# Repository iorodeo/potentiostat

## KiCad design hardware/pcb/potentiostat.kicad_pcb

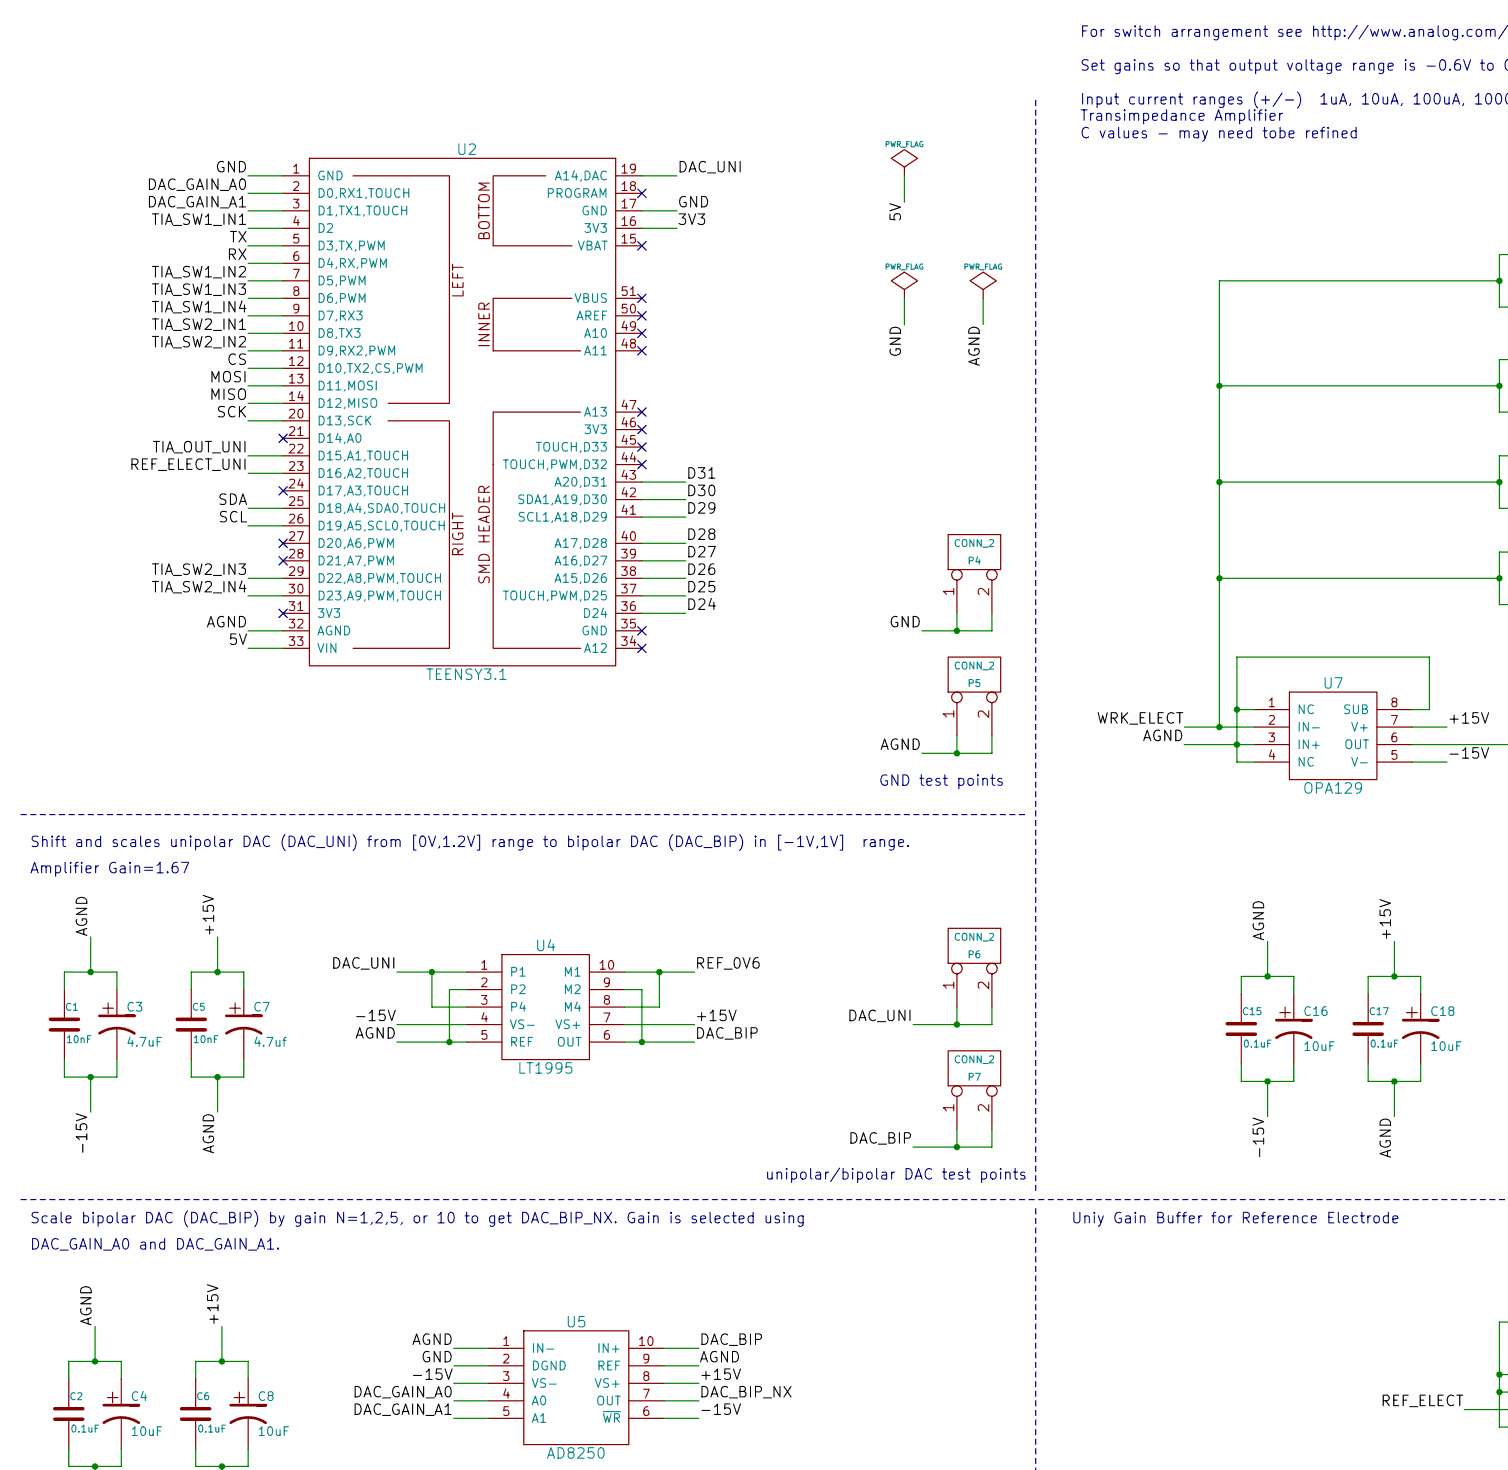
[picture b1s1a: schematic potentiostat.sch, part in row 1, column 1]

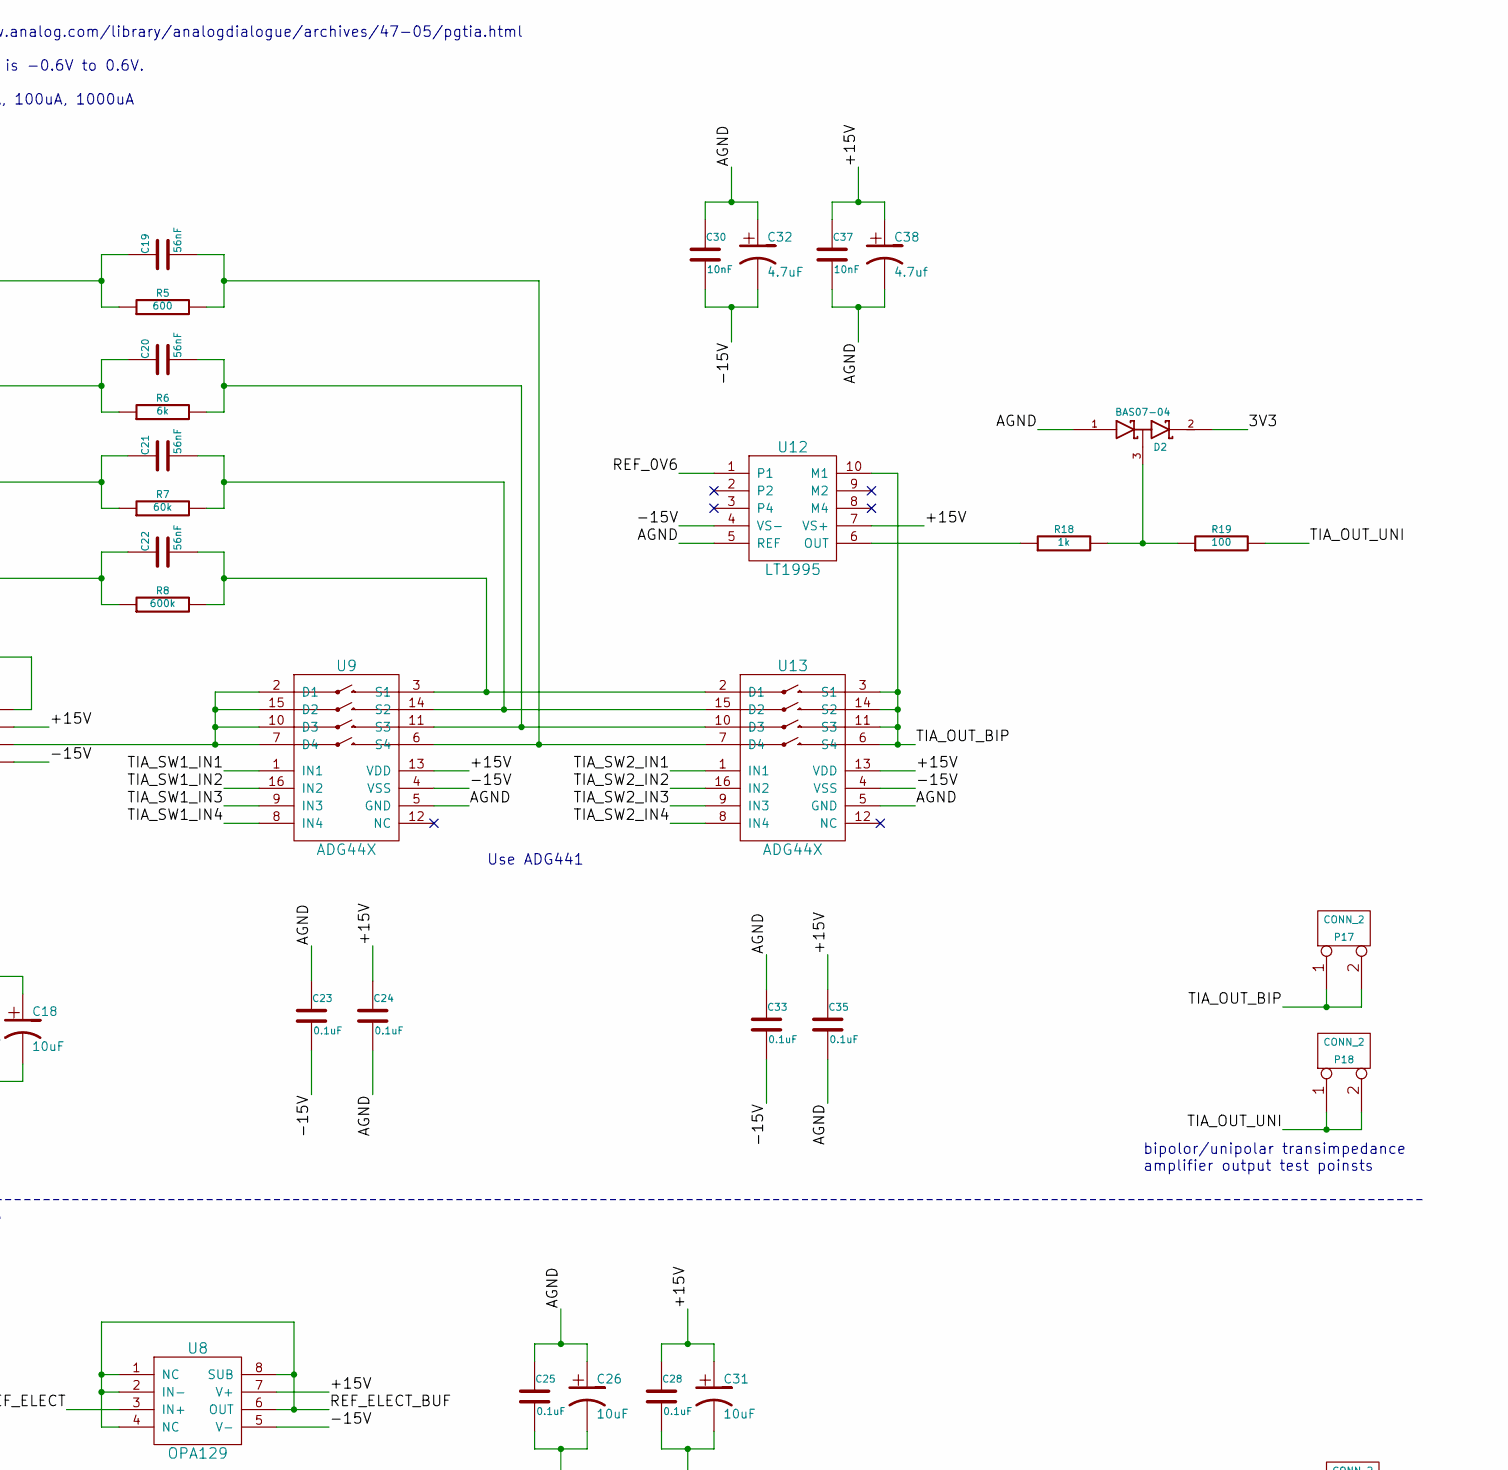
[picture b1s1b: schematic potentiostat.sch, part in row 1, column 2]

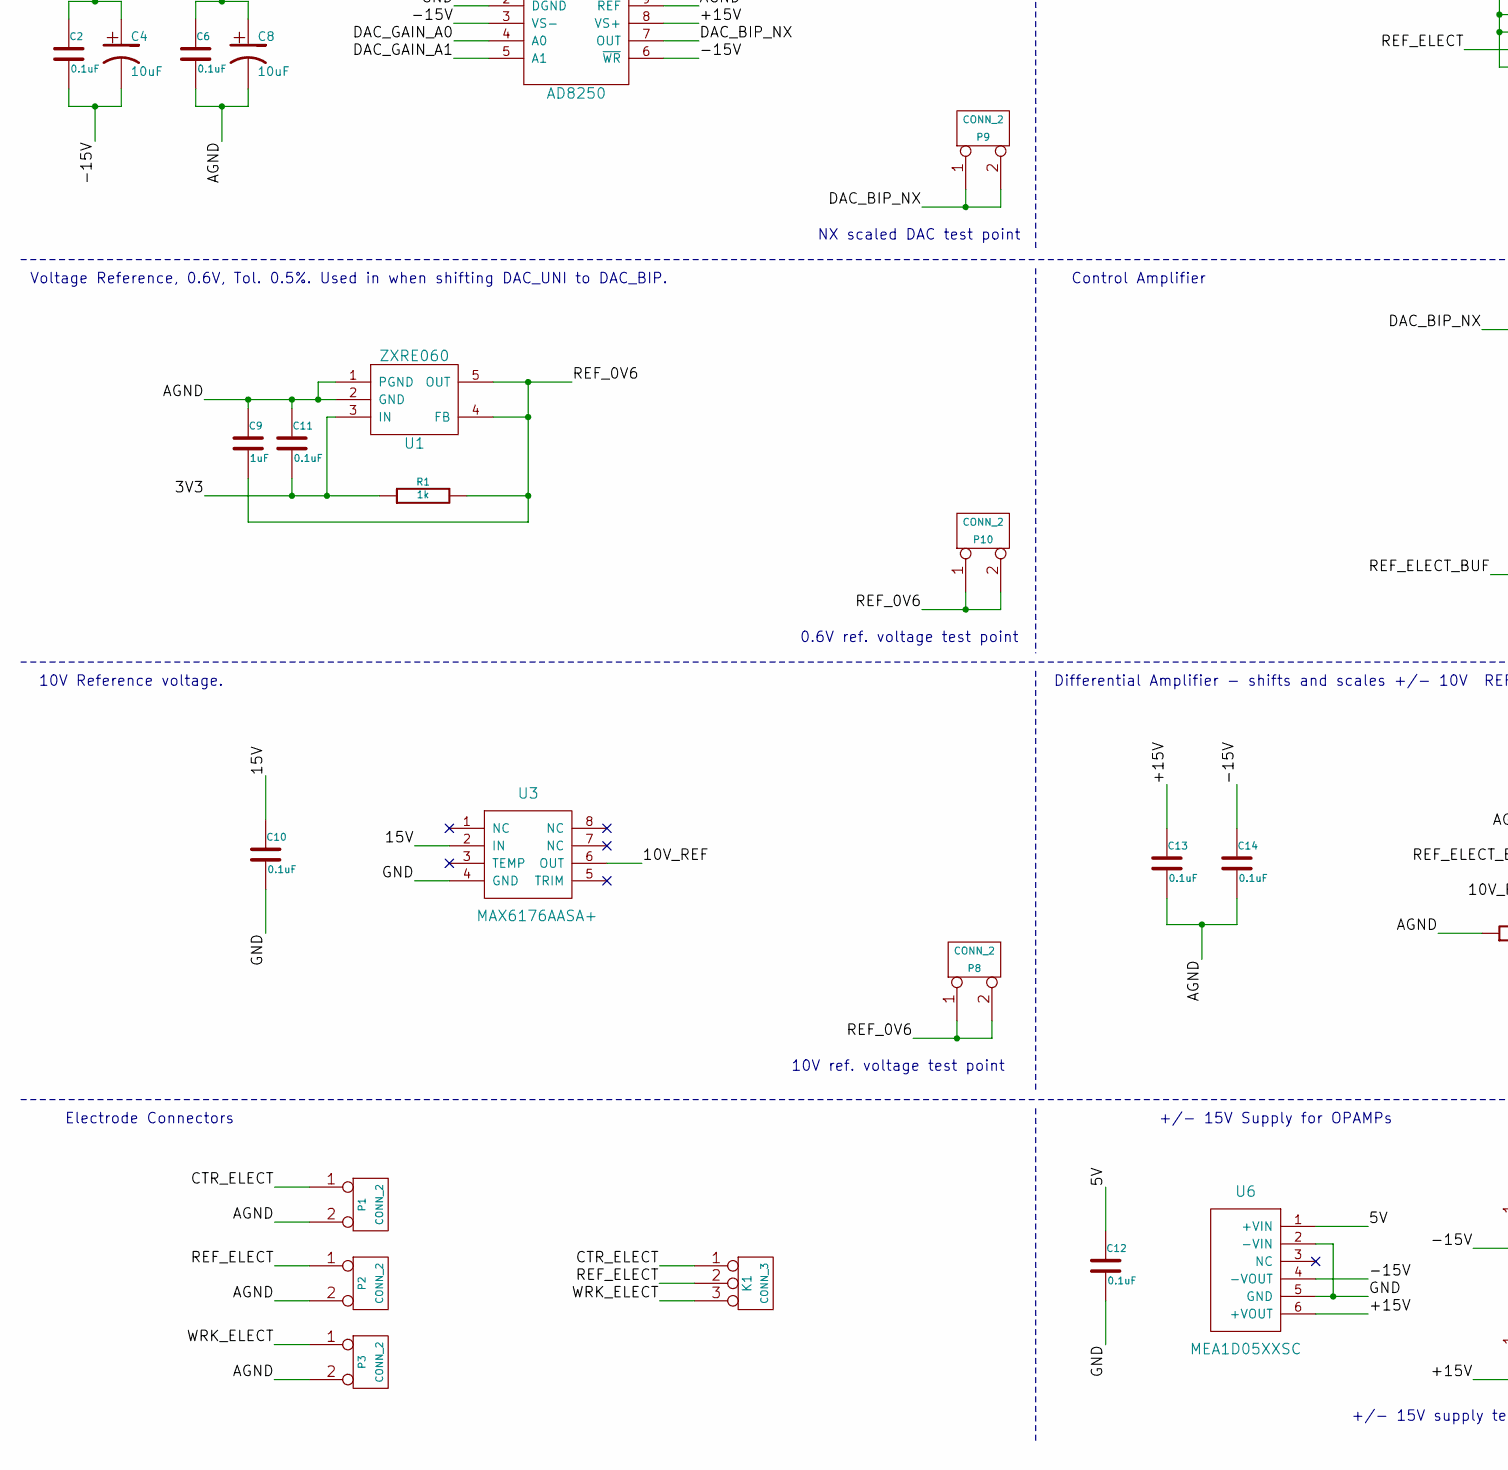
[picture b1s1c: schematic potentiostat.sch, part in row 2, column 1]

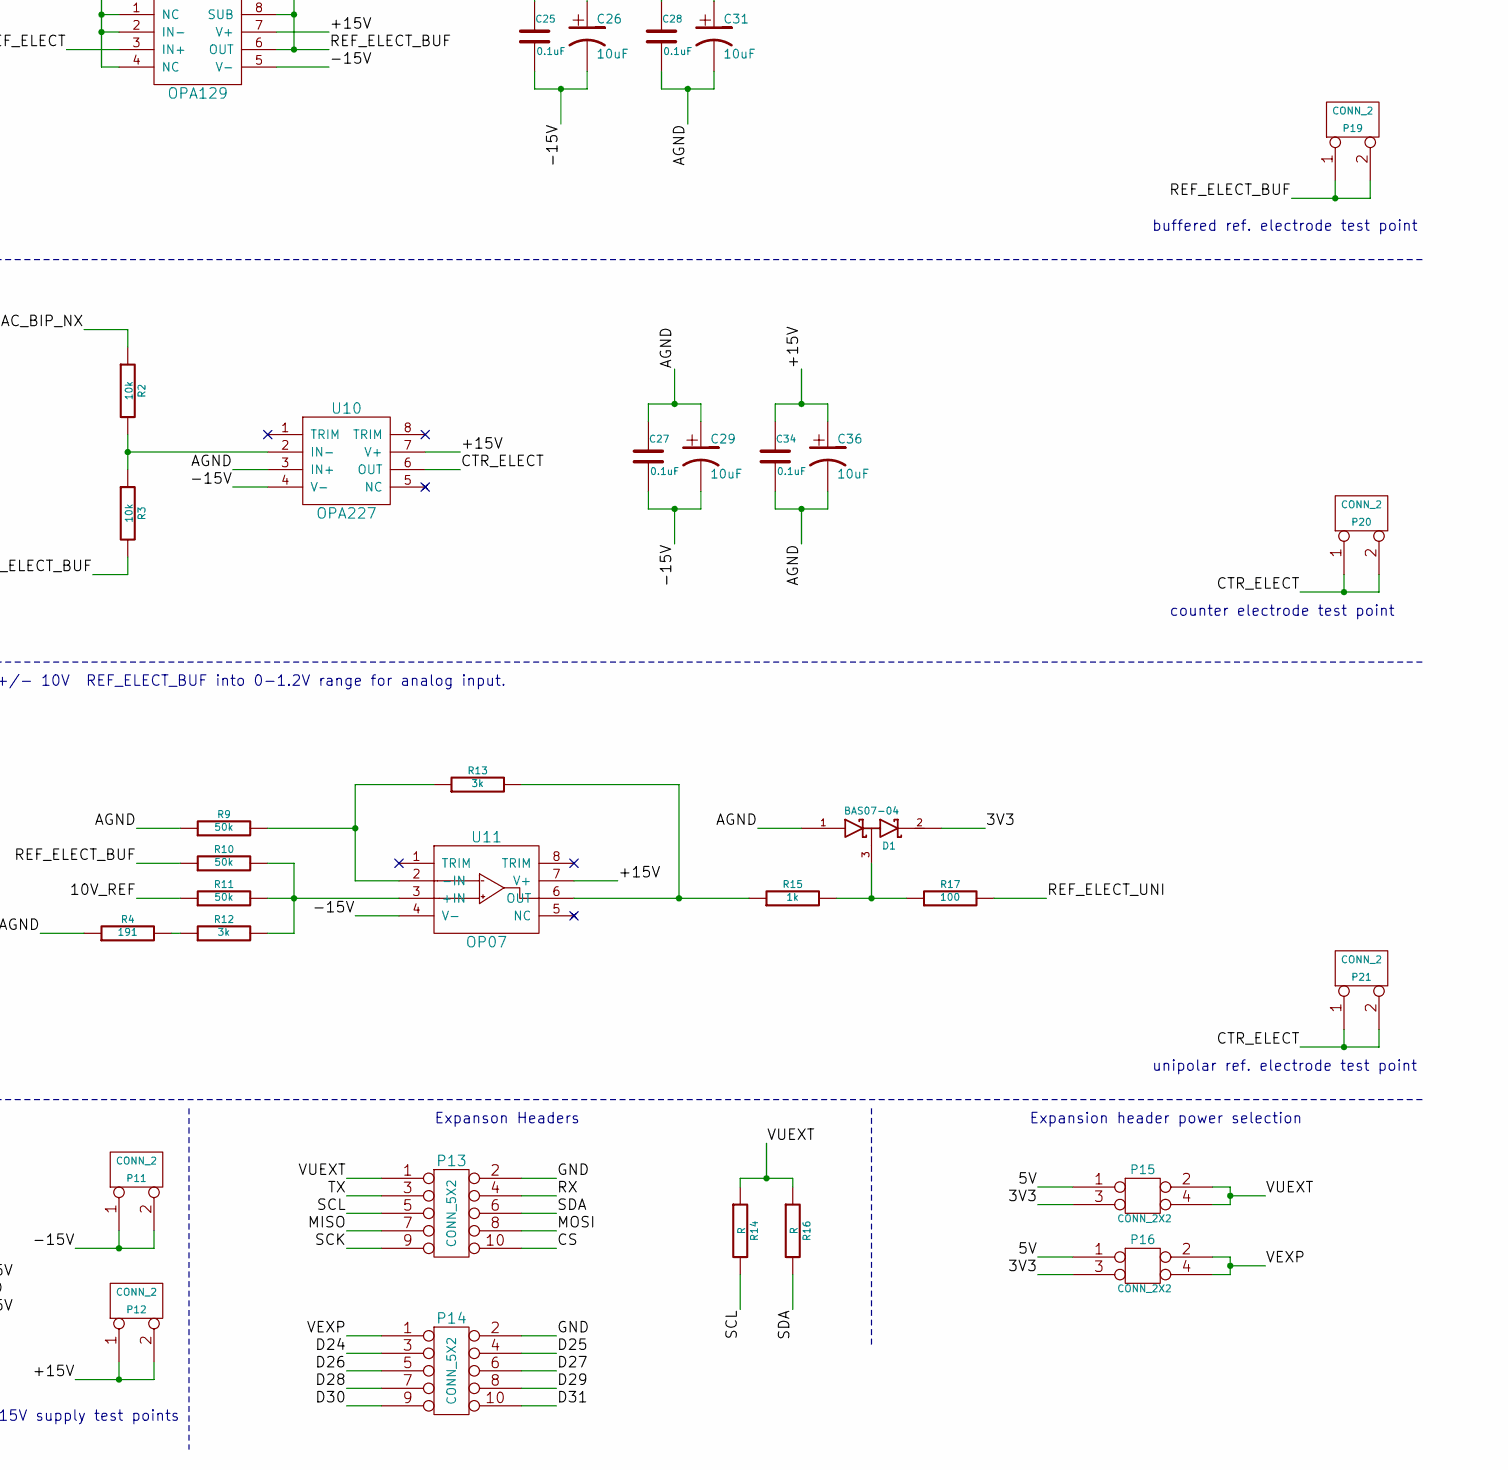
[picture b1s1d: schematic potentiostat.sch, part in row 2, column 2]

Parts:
C1, C5, C30, C37: 10nF
C2, C6, C10, C11, C12, C13, C14, C15, C17, C23, C24, C25, C27, C28, C33, C34, C35: 0.1uF
C3, C32: 4.7uF
C4, C8, C16, C18, C26, C29, C31, C36: 10uF
C7, C38: 4.7uf
C9: 1uF
C19, C20, C21, C22: 56nF
D1, D2: BAS07-04
K1: CONN_3
P1, P2, P3, P4, P5, P6, P7, P8, P9, P10, P11, P12, P17, P18, P19, P20, P21: CONN_2
P13, P14: CONN_5X2
P15, P16: CONN_2X2
R1, R15, R18: 1k
R2, R3: 10k
R4: 191
R5: 600
R6: 6k
R7: 60k
R8: 600k
R9, R10, R11: 50k
R12, R13: 3k
R14, R16: R
R17, R19: 100
U1: ZXRE060
U2: TEENSY3.1
U3: MAX6176AASA+
U4, U12: LT1995
U5: AD8250
U6: MEA1D05XXSC
U7, U8: OPA129
U9, U13: ADG44X
U10: OPA227
U11: OP07

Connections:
/3V3: C11.2, D1.2 (cathode), D2.2 (cathode), P15.3, P16.3, R1.1, U1.3 (IN), U2.16 (3V3)
/5V: C12.1, P15.1, P16.1, U2.33 (VIN), U6.1 (+VIN)
/15V: C10.1, U3.2 (IN)
/+15V: C5.1, C6.1, C7.1, C8.1, C13.1, C17.1, C18.1, C24.1, C28.1, C31.1, C34.1, C35.1, C36.1, C37.1, C38.1, P12.1, P12.2 (PM), U4.7 (VS+), U5.8 (VS+), U6.6 (+VOUT), U7.7 (V+), U8.7 (V+), U9.13 (VDD), U10.7 (V+), U11.7 (V+), U12.7 (VS+), U13.13 (VDD)
/-15V: C1.2, C2.2, C3.2, C4.2, C14.1, C15.2, C16.2, C23.2, C25.2, C26.2, C27.2, C29.2, C30.2, C32.2, C33.2, P11.1, P11.2 (PM), U4.4 (VS-), U5.3 (VS-), U5.6 (~WR), U6.4 (-VOUT), U7.5 (V-), U8.5 (V-), U9.4 (VSS), U10.4 (V-), U11.4 (V-), U12.4 (VS-), U13.4 (VSS)
/AGND: C1.1, C2.1, C3.1, C4.1, C5.2, C6.2, C7.2, C8.2, C9.1, C11.1, C13.2, C14.2, C15.1, C16.1, C17.2, C18.2, C23.1, C24.2, C25.1, C26.1, C27.1, C28.2, C29.1, C30.1, C31.2, C32.1, C33.1, C34.2, C35.2, C36.2, C37.2, C38.2, D1.1 (Anode), D2.1 (Anode), P1.2 (PM), P2.2 (PM), P3.2 (PM), P5.1, P5.2 (PM), R4.1, R9.1, U1.1 (PGND), U1.2 (GND), U2.32 (AGND), U4.2, U4.5 (REF), U5.1 (IN-), U5.9 (REF), U7.1 (NC), U7.3 (IN+), U7.4 (NC), U7.8 (SUB), U9.5 (GND), U10.3 (IN+), U12.5 (REF), U13.5 (GND)
/CS: P13.10, U2.12 (D10,TX2,CS,PWM)
/D24: P14.3, U2.36 (D24)
/D25: P14.4, U2.37 (TOUCH,PWM,D25)
/D26: P14.5, U2.38 (A15,D26)
/D27: P14.6, U2.39 (A16,D27)
/D28: P14.7, U2.40 (A17,D28)
/D29: P14.8, U2.41 (SCL1,A18,D29)
/D30: P14.9, U2.42 (SDA1,A19,D30)
/D31: P14.10, U2.43 (A20,D31)
/DAC_BIP: P7.1, P7.2 (PM), U4.6 (OUT), U4.9 (M2), U5.10 (IN+)
/DAC_BIP_NX: P9.1, P9.2 (PM), R2.1, U5.7 (OUT)
/DAC_GAIN_A0: U2.2 (D0,RX1,TOUCH), U5.4 (A0)
/DAC_GAIN_A1: U2.3 (D1,TX1,TOUCH), U5.5 (A1)
/DAC_UNI: P6.1, P6.2 (PM), U2.19 (A14,DAC), U4.1, U4.3 (P4)
/GND: C10.2, C12.2, P4.1, P4.2 (PM), P13.2, P14.2, U2.1 (GND), U2.17 (GND), U3.4 (GND), U5.2 (DGND), U6.2 (-VIN), U6.5 (GND)
/MISO: P13.7, U2.14 (D12,MISO)
/MOSI: P13.8, U2.13 (D11,MOSI)
/REF_ELECT: K1.2 (PM), P2.1, U8.3 (IN+)
/REF_ELECT_BUF: P19.1, P19.2 (PM), R3.2, R10.1, U8.1 (NC), U8.2 (IN-), U8.4 (NC), U8.6 (OUT), U8.8 (SUB)
/RX: P13.4, U2.6 (D4,RX,PWM)
/SCK: P13.9, U2.20 (D13,SCK)
/SCL: P13.5, R14.2, U2.26 (D19,A5,SCL0,TOUCH)
/SDA: P13.6, R16.2, U2.25 (D18,A4,SDA0,TOUCH)
/TIA_OUT_BIP: P17.1, P17.2 (PM), U12.10 (M1), U13.3 (S1), U13.6 (S4), U13.11 (S3), U13.14 (S2)
/TIA_OUT_UNI: P18.1, P18.2 (PM), R19.2, U2.22 (D15,A1,TOUCH)
/TIA_SW1_IN1: U2.4 (D2), U9.1 (IN1)
/TIA_SW1_IN2: U2.7 (D5,PWM), U9.16 (IN2)
/TIA_SW1_IN3: U2.8 (D6,PWM), U9.9 (IN3)
/TIA_SW1_IN4: U2.9 (D7,RX3), U9.8 (IN4)
/TIA_SW2_IN1: U2.10 (D8,TX3), U13.1 (IN1)
/TIA_SW2_IN2: U2.11 (D9,RX2,PWM), U13.16 (IN2)
/TIA_SW2_IN3: U2.29 (D22,A8,PWM,TOUCH), U13.9 (IN3)
/TIA_SW2_IN4: U2.30 (D23,A9,PWM,TOUCH), U13.8 (IN4)
/TX: P13.3, U2.5 (D3,TX,PWM)
/VEXP: P14.1, P16.2, P16.4
/VUEXT: P13.1, P15.2, P15.4, R14.1, R16.1
/WRK_ELECT: C19.1, C20.1, C21.1, C22.1, K1.3, P3.1, R5.1, R6.1, R7.1, R8.1, U7.2 (IN-)
unnamed: R18.1, U12.6 (OUT)
unnamed: D2.3 (AK), R18.2, R19.1
unnamed: U7.6 (OUT), U9.2 (D1), U9.7 (D4), U9.10 (D3), U9.15 (D2)
unnamed: R9.2, R13.1, U11.2 (-IN)
unnamed: R4.2, R12.1
unnamed: D1.3 (AK), R15.2, R17.1
unnamed: R13.2, R15.1, U11.6 (OUT)
unnamed: R10.2, R11.2, R12.2, U11.3 (+IN)
unnamed: C19.2, R5.2, U9.6 (S4), U13.7 (D4)
unnamed: C20.2, R6.2, U9.11 (S3), U13.10 (D3)
unnamed: C21.2, R7.2, U9.14 (S2), U13.15 (D2)
unnamed: C22.2, R8.2, U9.3 (S1), U13.2 (D1)
unnamed: R2.2, R3.1, U10.2 (IN-)

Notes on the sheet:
Voltage Reference, 0.6V, Tol. 0.5%. Used in when shifting DAC_UNI to DAC_BIP.
Shift and scales unipolar DAC (DAC_UNI) from [0V,1.2V] range to bipolar DAC (DAC_BIP) in [-1V,1V] range.
Scale bipolar DAC (DAC_BIP) by gain N=1,2,5, or 10 to get DAC_BIP_NX. Gain is selected using
DAC_GAIN_A0 and DAC_GAIN_A1.
Amplifier Gain=1.67
+/- 15V Supply for OPAMPs
Uniy Gain Buffer for Reference Electrode
Control Amplifier
Transimpedance Amplifier
Expanson Headers
Expansion header power selection
Electrode Connectors
For switch arrangement see http://www.analog.com/library/analogdialogue/archives/47-05/pgtia.html Set gains so that output voltage range is -0.6V to 0.6V. Input current ranges (+/-) 1uA, 10uA, 100uA, 1000uA C values - may need tobe refined
GND test points
unipolar/bipolar DAC test points
NX scaled DAC test point
0.6V ref. voltage test point
+/- 15V supply test points
buffered ref. electrode test point
bipolor/unipolar transimpedance amplifier output test poinsts
unipolar ref. electrode test point
10V Reference voltage.
10V ref. voltage test point
Differential Amplifier - shifts and scales +/- 10V REF_ELECT_BUF into 0-1.2V range for analog input.
counter electrode test point
Use ADG441

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
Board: 2 copper layers, 98 parts (0 on the bottom side), 60 nets, no tracks yet.

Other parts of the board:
4-40, 4-40#2, 4-40#3, 4-40#4: VAL**; 4-40

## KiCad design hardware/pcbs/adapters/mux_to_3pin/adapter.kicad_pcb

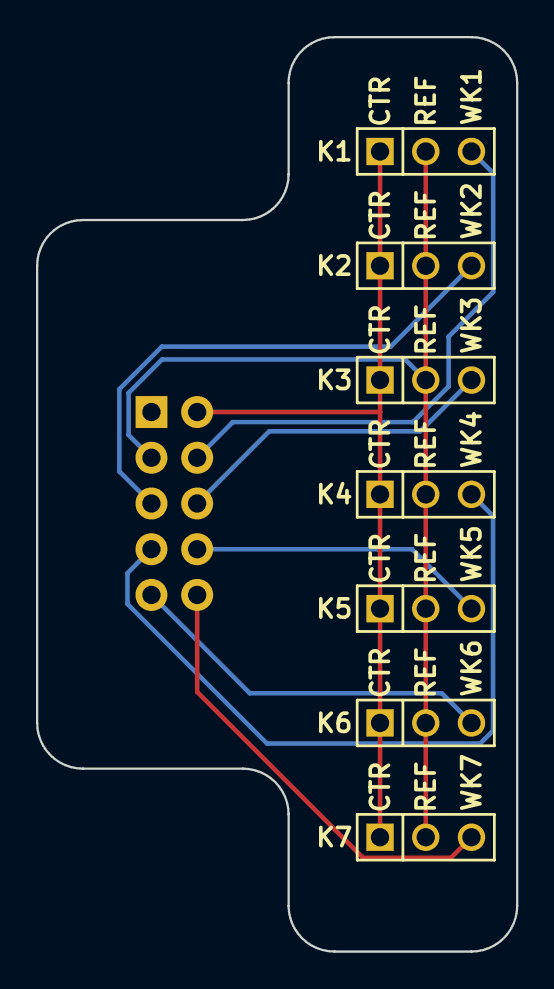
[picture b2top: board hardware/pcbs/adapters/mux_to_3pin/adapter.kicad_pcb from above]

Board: 2 copper layers, 26.7 x 50.8 mm, 8 parts (1 on the bottom side), 9 nets.

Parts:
K1, K2, K3, K4, K5, K6, K7: CONN_3; PIN_ARRAY_3X1
P1: CONN_5X2; 5X2_SHRD_HEADER_FEMALE

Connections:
/CTR_SW: K1.1, K2.1, K3.1, K4.1, K5.1, K6.1, K7.1, P1.2
/REF_SW: K1.2, K2.2, K3.2, K4.2, K5.2, K6.2, K7.2, P1.3
/WRK_1: K1.3, P1.4
/WRK_2: K2.3, P1.5
/WRK_3: K3.3, P1.6
/WRK_4: K4.3, P1.7
/WRK_5: K5.3, P1.8
/WRK_6: K6.3, P1.9
/WRK_7: K7.3, P1.10

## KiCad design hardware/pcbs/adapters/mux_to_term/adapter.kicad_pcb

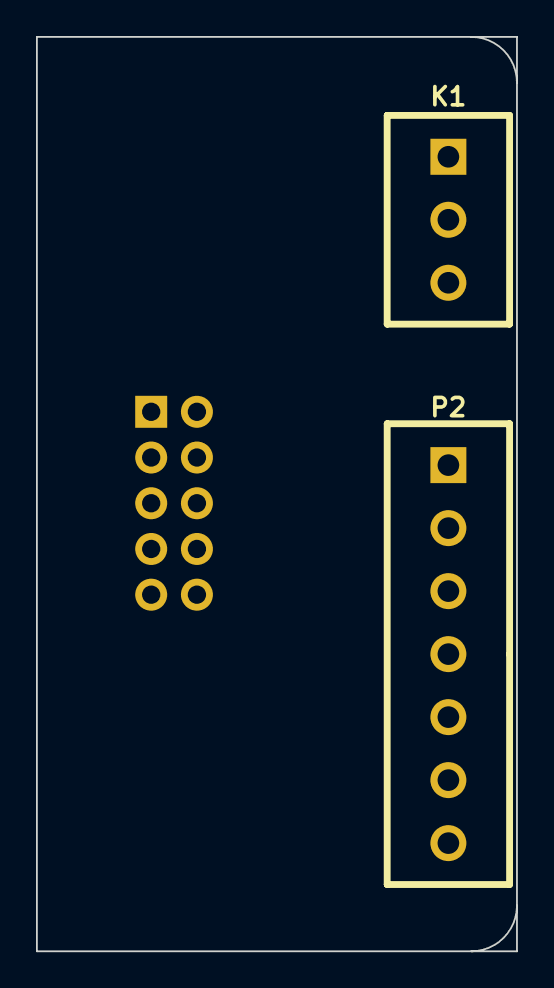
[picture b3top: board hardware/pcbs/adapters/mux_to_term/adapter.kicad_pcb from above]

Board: 2 copper layers, 26.7 x 50.8 mm, 3 parts (1 on the bottom side), 10 nets, no tracks yet.

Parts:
K1: CONN_3; CONNBLOCK3
P1: CONN_5X2; 5X2_SHRD_HEADER_FEMALE
P2: CONN_7; CONNBLOCK7

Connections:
/CTR_SW: K1.2, P1.2
/GND: K1.1, P1.1
/REF_SW: K1.3, P1.3
/WRK_1: P1.4, P2.1
/WRK_2: P1.5, P2.2
/WRK_3: P1.6, P2.3
/WRK_4: P1.7, P2.4
/WRK_5: P1.8, P2.5
/WRK_6: P1.9, P2.6
/WRK_7: P1.10, P2.7

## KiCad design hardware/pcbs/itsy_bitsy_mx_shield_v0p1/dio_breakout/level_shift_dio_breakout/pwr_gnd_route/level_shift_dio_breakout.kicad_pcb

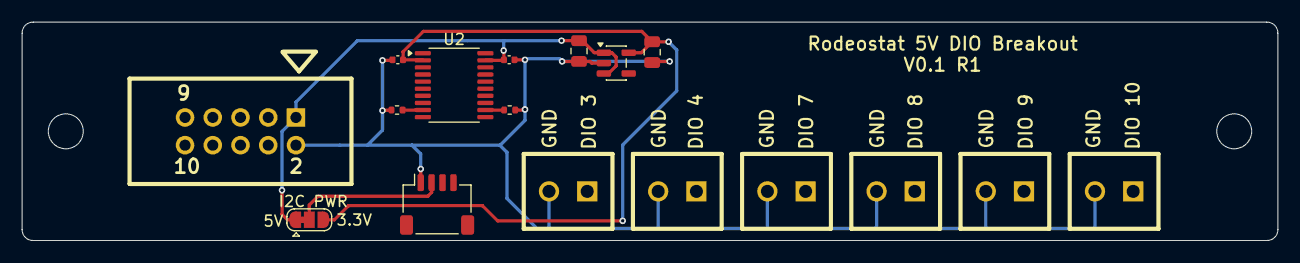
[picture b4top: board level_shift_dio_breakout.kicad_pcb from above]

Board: 2 copper layers, 115.0 x 20.0 mm, 19 parts (0 on the bottom side), 20 nets.

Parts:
C1, C2: 10uF; C_0805_2012Metric
C3, C4: 0.1uF; C_0402_1005Metric
H1, H2: MountingHole; MountingHole_3.2mm_M3
J1: Conn_02x05_Odd_Even; 5X2_SHRD_HEADER
J2: Conn_01x04; JST_SH_SM04B-SRSS-TB_1x04-1MP_P1.00mm_Horizontal
J3, J4, J5, J6, J7, J8: Screw_Terminal_01x02; CONNBLOCK2
JP1: SolderJumper_3_Bridged12; SolderJumper-3_P1.3mm_Bridged12_RoundedPad1.0x1.5mm
R1, R2: 10k; R_0402_1005Metric
U1: AP2112K-3.3; SOT-23-5
U2: TXB0108PW; TSSOP-20_4.4x6.5mm_P0.65mm

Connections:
+3.3V: C2.1, C3.1, JP1.3 (B), U1.5 (VOUT), U2.2 (V_{CCA}), U2.10 (OE)
+5V: C1.1, C4.1, J1.1, JP1.1 (A), U1.1 (VIN), U1.3 (EN), U2.19 (V_{CCB})
/DIO_PIN_3: J1.3, U2.1 (A1)
/DIO_PIN_4: J1.4, U2.3 (A2)
/DIO_PIN_5: J1.5, J2.4
/DIO_PIN_6: J1.6, J2.3
/DIO_PIN_7: J1.7, U2.4 (A3)
/DIO_PIN_8: J1.8, U2.5 (A4)
/DIO_PIN_9: J1.9, U2.6 (A5)
/DIO_PIN_10: J1.10, U2.7 (A6)
/V_I2C: J2.2, JP1.2 (C)
GND: C1.2, C2.2, C3.2, C4.2, J1.2, J2.1, J3.2, J4.2, J5.2, J6.2, J7.2, J8.2, R1.2, R2.2, U1.2 (GND), U2.11 (GND)
unnamed: J3.1, U2.20 (B1)
unnamed: J4.1, U2.18 (B2)
unnamed: J5.1, U2.17 (B3)
unnamed: J6.1, U2.16 (B4)
unnamed: J7.1, U2.15 (B5)
unnamed: J8.1, U2.14 (B6)
unnamed: R1.1, U2.8 (A7), U2.9 (A8)
unnamed: R2.1, U2.12 (B8), U2.13 (B7)

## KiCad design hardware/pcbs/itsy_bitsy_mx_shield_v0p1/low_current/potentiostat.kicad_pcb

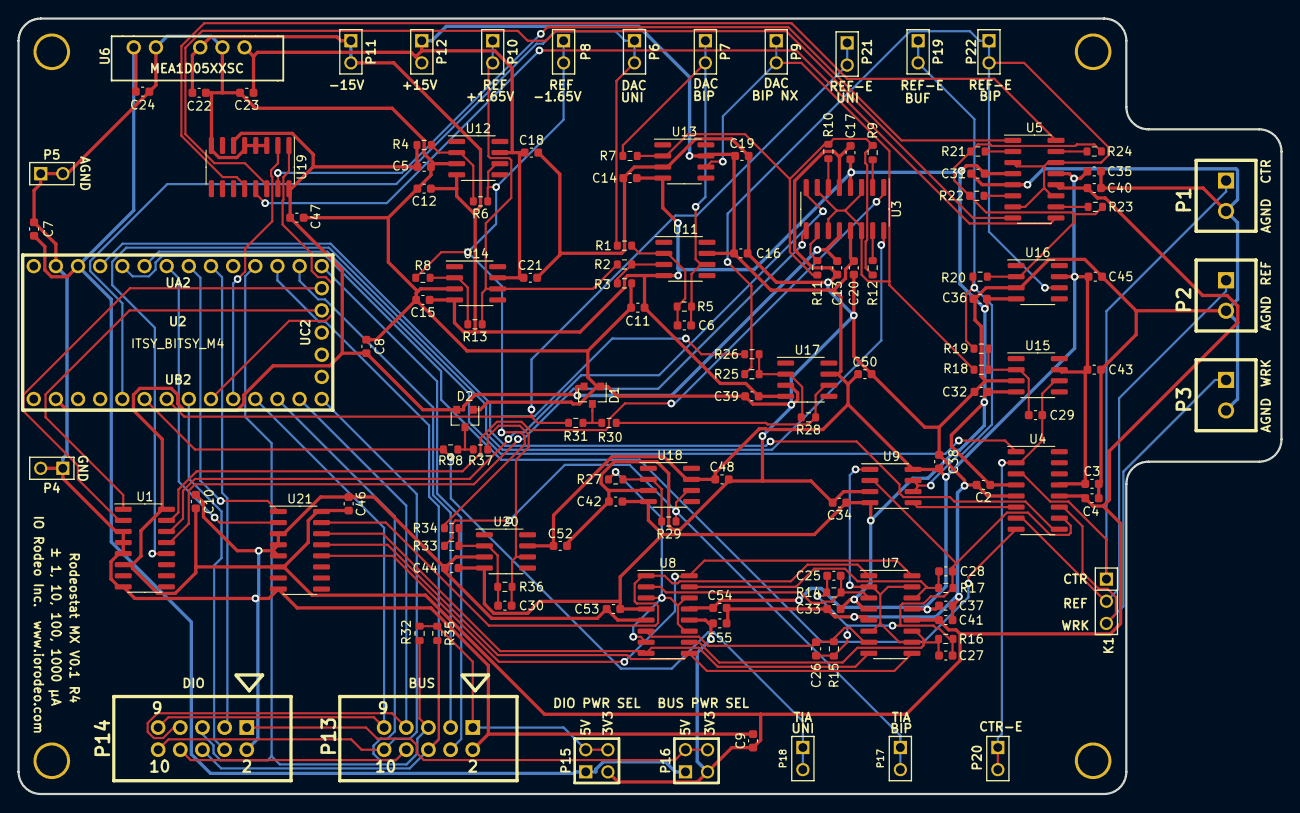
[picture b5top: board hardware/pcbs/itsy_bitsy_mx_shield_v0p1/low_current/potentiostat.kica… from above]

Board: 2 copper layers, 144.8 x 88.9 mm, 142 parts (0 on the bottom side), 82 nets.

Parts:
C2, C3, C4, C10, C11, C12, C13, C14, C15, C16, C17, C18, C19, C20, C21, C24, C31, C32, C33, C34, C35, C36, C37, C38, C39, C40, C41, C42, C43, C44, C45, C46, C47, C48, C50, C52, C53, C54, C55: 0.1uF; C_0603_1608Metric
C5: 4.7uF; C_0603_1608Metric
C6: 3.3nF; C_0603_1608Metric
C7, C8, C9: 2.2uF; C_0603_1608Metric
C22, C23: 1uF; C_0603_1608Metric
C25, C26, C27, C28: 56nF; C_0603_1608Metric
C29: 10nF; C_0603_1608Metric
C30: 12nF; C_0603_1608Metric
D1, D2: BAS07-04; SOT-23
H1, H2, H3, H4: VAL**; 4-40
K1: Conn_01x03; PIN_ARRAY_3X1
P1, P2, P3: Conn_01x02; CONNBLOCK2
P4, P5, P6, P7, P8, P9, P10, P11, P12, P17, P18, P19, P20, P21, P22: Conn_01x02; PIN_ARRAY_2X1
P13, P14: Conn_02x05_Odd_Even; 5X2_SHRD_HEADER
P15, P16: Conn_02x02_Odd_Even; PIN_ARRAY_2X2
R1, R2, R26, R28: 33k; R_0603_1608Metric
R3, R4, R5, R8, R10, R13, R23, R25: 20k; R_0603_1608Metric
R6, R7, R9, R18, R19, R24, R33, R34, R36: 10k; R_0603_1608Metric
R11, R22: 50k; R_0603_1608Metric
R12, R20, R21: 100k; R_0603_1608Metric
R14: 300k; R_0603_1608Metric
R15: 30k; R_0603_1608Metric
R16: 3k; R_0603_1608Metric
R17: 300; R_0603_1608Metric
R27: 2k; R_0603_1608Metric
R29: 11k; R_0603_1608Metric
R30, R37: 1k; R_0603_1608Metric
R31, R38: 100; R_0603_1608Metric
R32, R35: 4.7k; R_0603_1608Metric
U1, U19, U21: 74HC138; SOIC-16_3.9x9.9mm_P1.27mm
U2: ITSY_BITSY_M4
U3, U4, U5, U7, U8: DG411xY; SOIC-16_3.9x9.9mm_P1.27mm
U6: MEA1D05XXSC; MEA1
U9: TL072; SOIC-8_3.9x4.9mm_P1.27mm
U11, U12, U13, U14, U15, U16, U17, U18, U20: OP07; SOIC-8_3.9x4.9mm_P1.27mm
UA2: header_14_pos
UB2: header_14_pos
UC2: header_5_pos

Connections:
/3V3: C4.1, C5.1, C8.1, C9.1, C10.1, C13.1, C40.1, C41.1, C46.1, C47.1, C55.1, D1.2, D2.2, P15.3, P16.3, R4.2, U1.6, U1.16, U2.2, U3.12, U4.12, U5.12, U7.12, U8.12, U19.6, U19.16, U21.6, U21.16
/5V: C7.1, C24.1, P15.1, P16.1, U2.31, U6.1
/+15V: C3.1, C16.1, C18.1, C19.1, C20.1, C21.1, C23.1, C35.1, C37.1, C38.1, C43.1, C45.1, C48.1, C50.1, C52.1, C54.1, P12.1, P12.2, U3.13, U4.13, U5.13, U6.6, U7.13, U8.13, U9.8, U11.7, U12.7, U13.7, U14.7, U15.7, U16.7, U17.7, U18.7, U20.7
/-15V: C2.1, C11.1, C12.1, C14.1, C15.1, C17.1, C22.1, C31.1, C32.1, C33.1, C34.1, C36.1, C39.1, C42.1, C44.1, C53.1, P11.1, P11.2, U3.4, U4.4, U5.4, U6.4, U7.4, U8.4, U9.4, U11.4, U12.4, U13.4, U14.4, U15.4, U16.4, U17.4, U18.4, U20.4
/A3_D17: P14.4, U2.8
/CS: P13.10, P14.10, U2.14
/CTR_ELECT: C29.1, P20.1, P20.2, U4.2, U15.6
/CTR_ELECT_OUT: K1.1, P1.1, U4.3
/D7: P14.3, U2.25
/DAC_BIP: C6.1, P7.1, P7.2, R5.1, R7.2, U11.6
/DAC_BIP_NX: P9.1, P9.2, R18.2, U3.3, U3.7, U3.11, U3.14, U13.6
/DAC_GAIN_A0: U1.1, U2.18
/DAC_GAIN_A1: U1.2, U2.19
/DAC_UNI: P6.1, P6.2, R1.2, U2.5
/GND: C2.2, C3.2, C4.2, C5.2, C7.2, C8.2, C9.2, C10.2, C11.2, C12.2, C13.2, C14.2, C15.2, C16.2, C17.2, C18.2, C19.2, C20.2, C21.2, C22.2, C23.2, C24.2, C31.2, C32.2, C33.2, C34.2, C35.2, C36.2, C37.2, C38.2, C39.2, C40.2, C41.2, C42.2, C43.2, C44.2, C45.2, C46.2, C47.2, C48.2, C50.2, C52.2, C53.2, C54.2, C55.2, D1.1, D2.1, P1.2, P2.2, P3.2, P4.1, P4.2, P5.1, P5.2, P13.2, P14.2, R3.2, U1.3, U1.4, U1.5, U1.8, U2.32, U3.5, U4.5, U5.5, U6.2, U6.5, U7.5, U8.5, U9.3, U12.3, U13.3, U14.3, U15.3, U16.3, U17.3, U18.3, U19.3, U19.4, U19.5, U19.8, U20.3, U21.3, U21.4, U21.5, U21.8
/PICO: P13.8, P14.8, U2.12
/POCI: P13.7, P14.7, U2.13
/REF_1V65: P10.1, P10.2, R2.2, R13.1, U14.6
/REF_ELECT: U4.6, U9.5
/REF_ELECT_BIP: P22.1, P22.2, R25.2, U5.3, U5.7, U5.11, U5.14, U16.6
/REF_ELECT_BUF: P19.1, P19.2, R19.1, R20.2, U9.6, U9.7
/REF_ELECT_OUT: K1.2, P2.1, U4.7
/REF_ELECT_UNI: P21.1, P21.2, R31.1, U2.7
/REF_GAIN_A0: U2.9, U19.1
/REF_GAIN_A1: U2.10, U19.2
/REF_NEG_1V65: P8.1, P8.2, R6.1, R8.2, R26.2, R34.2, U12.6
/RX_D0: P13.4, U2.20
/SCK: P13.9, P14.9, U2.11
/SCL: P13.5, P14.5, R32.2, U2.23
/SDA: P13.6, P14.6, R35.2, U2.22
/SW_CTR_ELECT: U2.28, U4.1
/SW_GAIN_1X: U1.15, U3.1
/SW_GAIN_2X: U1.14, U3.8
/SW_GAIN_5X: U1.13, U3.9
/SW_GAIN_10X: U1.12, U3.16
/SW_GAIN_INV_1X: U5.1, U19.15
/SW_GAIN_INV_2X: U5.8, U19.14
/SW_GAIN_INV_5X: U5.9, U19.13
/SW_GAIN_INV_10X: U5.16, U19.12
/SW_REF_ELECT: U2.29, U4.8
/SW_TIA_GAIN_1: U7.1, U8.1, U21.15
/SW_TIA_GAIN_2: U7.8, U8.8, U21.14
/SW_TIA_GAIN_3: U7.9, U8.9, U21.13
/SW_TIA_GAIN_4: U7.16, U8.16, U21.12
/SW_WRK_ELECT: U2.30, U4.9
/TIA_GAIN_A0: U2.26, U21.1
/TIA_GAIN_A1: U2.27, U21.2
/TIA_OUT_BIP: P17.1, P17.2, R29.1, R33.2, U18.6
/TIA_OUT_UNI: P18.1, P18.2, R38.1, U2.6
/TX_D1: P13.3, U2.21
/VEXP: P14.1, P16.2, P16.4
/VUEXT: P13.1, P15.2, P15.4, R32.1, R35.1
/WRK_ELECT: C25.2, C26.2, C27.2, C28.2, R14.2, R15.2, R16.2, R17.2, U4.10, U9.2
/WRK_ELECT_OUT: K1.3, P3.1, U4.11
unnamed: C6.2, R1.1, R5.2, U11.2
unnamed: C25.1, R14.1, U7.3, U8.2
unnamed: C26.1, R15.1, U7.7, U8.6
unnamed: C27.1, R16.1, U7.11, U8.10
unnamed: C28.1, R17.1, U7.14, U8.15
unnamed: C29.2, R18.1, R19.2, U15.2
unnamed: C30.1, R36.1, R37.2, U20.6
unnamed: C30.2, R33.1, R34.1, R36.2, U20.2
unnamed: D1.3, R30.1, R31.2
unnamed: D2.3, R37.1, R38.2
unnamed: R2.1, R3.1, U11.3
unnamed: R4.1, R6.2, U12.2
unnamed: R9.1, U3.2
unnamed: R10.1, U3.6
unnamed: R7.1, R9.2, R10.2, R11.2, R12.2, U13.2
unnamed: R11.1, U3.10
unnamed: R12.1, U3.15
unnamed: R8.1, R13.2, U14.2
unnamed: R20.1, R21.2, R22.2, R23.2, R24.2, U16.2
unnamed: R21.1, U5.2
unnamed: R22.1, U5.6
unnamed: R23.1, U5.10
unnamed: R24.1, U5.15
unnamed: R25.1, R26.1, R28.2, U17.2
unnamed: R27.1, R29.2, U18.2
unnamed: R27.2, U8.3, U8.7, U8.11, U8.14
unnamed: R28.1, R30.2, U17.6
unnamed: U7.2, U7.6, U7.10, U7.15, U9.1

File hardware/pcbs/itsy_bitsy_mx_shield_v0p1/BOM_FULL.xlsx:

JLCPCB
Comment | Designator | Footprint | LCSC Part #（optional） | Qty
4.7uF ceramic capacitor | C5 | 603 | C19666 | 2
0.1uF ceramic capacitor | C2,C3,C4,C10,C11,C12,C13,C14,C15,C16,C17,C18,C19,C20,C21,C24,C31,C32,C33,C34,C3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 | 603 | C14663 | 39
3.3nF ceramic capacitor | C6 | 603 | C170145 | 1
2.2uF ceramic capacitor | C7,C8,C9 | 603 | C23630 | 3
1uF ceramic capacitor | C22,C23 | 603 | C15849 | 2
56nF ceramic capacitor | C25,C26,C27,C28 | 603 | C31658 | 4
10nF ceramic capacitor | C29 | 603 | C57112 | 1
12nF ceramic capacitor | C30 | 603 | C1593 | 1
BAS70-04 Schottky Barrier Diodes | D1,D2 | SOT-23 | C609810 | 2
12k Resistor, 1% | R1,R2,R26,R28,R34,R36,R33 | 603 | C22790 | 7
20k Resistor, 1% | R3,R5,R6,R8,R10,R13,R23,R25,R29 | 603 | C4184 | 9
100k Resistor, 1% | R4,R12,R20,R21 | 603 | C25803 | 4
10k Resistor, 1% | R7,R9,R18,R19,R24,R27 | 603 | C25804 | 6
49.9k Resistor, 1% | R11,R22 | 603 | C23184 | 2
300k Resistor, 1% | R14 | 603 | C23024 | 1
30k Resistor, 1% | R15 | 603 | C22984 | 1
3k Resistor, 1% | R16 | 603 | C4211 | 1
300 Ohm Resistor, 1% | R17 | 603 | C23025 | 1
1k Resistor, 1% | R30,R37 | 603 | C21190 | 2
100 Ohm Resistor | R31,R38 | 603 | C22775 | 2
4.7k Resistor | R32,R35 | 603 | C23162 | 2
74HC138 3-to-8 line decoder/demultiplexer | U1,U19,U21 | SOIC-16_3.9x9.9x1.27P | C5602 | 3
DG411DY-T1-E3 Quad Analog Switches | U3,U4,U5,U7,U8 | SOIC-16_3.9x9.9x1.27P | C17218 | 5
TL072CDT Dual JFET-Input Operational Amplifiers | U9 | SOIC-8_3.9x4.9x1.27P | C6961 | 1
OP07CDR Precision Operational Amplifier | U11,U12,U13,U14,U15,U16,U17,U18,U20 | SOIC-8_3.9x4.9x1.27P | C7433 | 9
Digikey
Comment | Designator | Footprint | Digikey Part #（optional） | Qty
3-pin right angle 0.1” pitch | K1 | NA | S1111EC-03-ND | 1
Break away header 40-pos 0.1” pitch | P1,P2,P3,P4,P5,P6,P7,P8,P9,P10,P11,P12,P17,P18,P19,P20,P21,P22 | NA | S1011EC-40-ND | 1
5x2 shrouded header, 0.1” | P13,P14 | NA | S9169-ND | 2
Header 4-Pos, 2 row, 0.1” | P15,P16 | NA | 609-3201-ND | 2
TEENSY3.2 | U2 | NA | 1568-1231-ND | 1
DC DC Converter 2 Output 15V -15V | U6 | NA | 811-2679-5-ND | 1
2-Pos. Term. Block, 3.5mm, Vert. | P1, P2, P2 | NA | ED2635-ND
